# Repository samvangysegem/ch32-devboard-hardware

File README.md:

# CH32 Development Board

This repository contains hardware design files and documentation for a development board based on the CH32V30x series of microcontrollers. The board features USB-FS and UART communication interfaces, as well as input current monitoring. It is intended as a test and development platform for projects using the CH32V30x family.

Documentation is available in the [docs](./docs) folder, including:
- [Component datasheets and specifications](./docs/01_specs/)
- [Design calculations](./docs/02_calcs/)

For compatible firmware, see the related firmware repository
➡️ [ch32-devboard-firmware](https://github.com/samvangysegem/ch32-devboard-firmware)

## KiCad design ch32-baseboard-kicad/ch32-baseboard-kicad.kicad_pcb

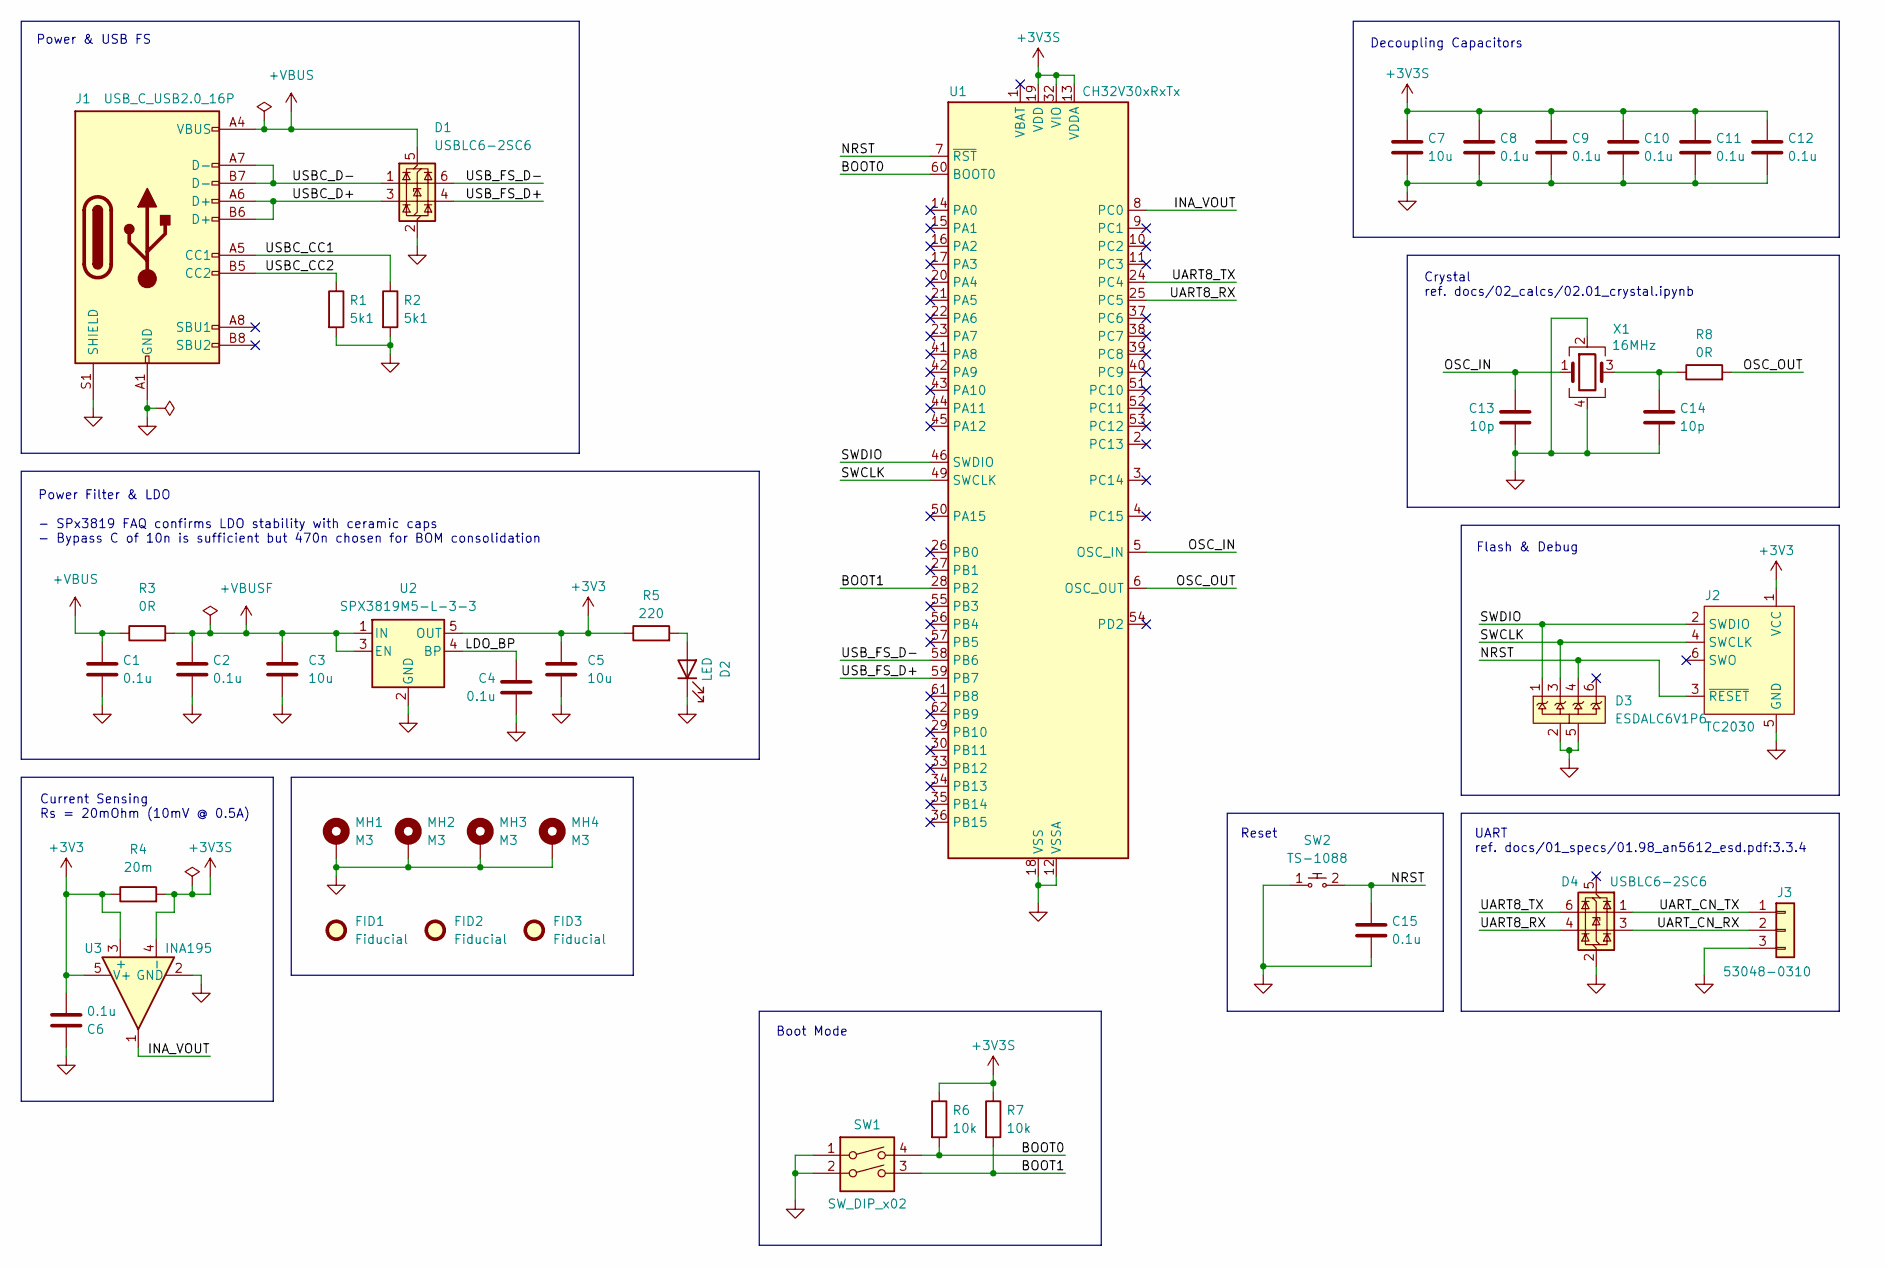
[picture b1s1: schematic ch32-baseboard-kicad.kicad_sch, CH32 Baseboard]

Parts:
C1, C2, C4, C6, C8, C9, C10, C11, C12, C15: 0.1u; C_0402_1005Metric; Manufacturer Part Number CL05B104KO5NNNC
C3, C5, C7: 10u; C_0805_2012Metric; Manufacturer Part Number CL21A106KAYNNNE
C13, C14: 10p; C_0402_1005Metric; Manufacturer Part Number CL05C100JB5NNNC
D1, D4: USBLC6-2SC6; SOT-23-6
D2: LED; LED_0603_1608Metric; Manufacturer Part Number KT-0603W
D3: ESDALC6V1P6; SOT-666IP-STM; Manufacturer Part Number ESDALC6V1P6
FID1, FID2, FID3: Fiducial; Fiducial_1mm_Mask2mm
J1: USB_C_USB2.0_16P; USB_C_Receptacle_GCT_USB4105-xx-A_16P_TopMnt_Horizontal; Manufacturer Part Number TYPE-C 16PIN 2MD(073); JLCPCB Part Number C2765186
J2: TC2030; Tag-Connect_TC2030-IDC-FP_2x03_P1.27mm_Vertical
J3: 53048-0310; Molex_PicoBlade_53048-0310_1x03_P1.25mm_Horizontal; Manufacturer Part Number 530480310
MH1, MH2, MH3, MH4: M3; MountingHole_3.2mm_M3_Pad_Via
R1, R2: 5k1; R_0402_1005Metric; Manufacturer Part Number 0402WGF5101TCE
R3: 0R; R_0805_2012Metric_Pad1.20x1.40mm_HandSolder; Manufacturer Part Number 0805W8F0000T5E
R4: 20m; R_1206_3216Metric; Manufacturer Part Number LR1206-21R020F4
R5: 220; R_0603_1608Metric; Manufacturer Part Number 0603WAF2200T5E
R6, R7: 10k; R_0603_1608Metric; Manufacturer Part Number 0603WAF1002T5E
R8: 0R; R_0402_1005Metric; Manufacturer Part Number 0402WGF0000TCE
SW1: SW_DIP_x02; SW_DIP_SPSTx02_Slide_6.7x6.64mm_W8.61mm_P2.54mm_LowProfile; Manufacturer Part Number SMXS-02K-TP
SW2: TS-1088; SW_SPST_TS-1088-xR020; Manufacturer Part Number TS-1088-AR02016
U1: CH32V30xRxTx; LQFP-64_10x10mm_P0.5mm; JLCPCB C2988083
U2: SPX3819M5-L-3-3; SOT-23-5; Manufacturer Part Number SPX3819M5-L-3-3/TR
U3: INA195; SOT-23-5
X1: 16MHz; Crystal_SMD_3225-4Pin_3.2x2.5mm; Manufacturer Part Number X322516MLB4SI

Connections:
+3V3: C5.1, C6.2, J2.1 (VCC), R4.1, R5.1, U2.5 (OUT), U3.3 (+), U3.5 (V+)
+3V3S: C7.1, C8.1, C9.1, C10.1, C11.1, C12.1, R4.2, R6.1, R7.1, U1.13 (VDDA), U1.19 (VDD), U1.32 (VIO), U1.48 (VDD), U1.64 (VIO), U3.4 (-)
+VBUS: C1.1, D1.5 (VBUS), J1.A4 (VBUS), J1.A9 (VBUS), J1.B4 (VBUS), J1.B9 (VBUS), R3.1
+VBUSF: C2.1, C3.1, R3.2, U2.1 (IN), U2.3 (EN)
/BOOT0: R6.2, SW1.4, U1.60 (BOOT0)
/BOOT1: R7.2, SW1.3, U1.28 (PB2)
/INA_VOUT: U1.8 (PC0), U3.1
/LDO_BP: C4.1, U2.4 (BP)
/NRST: C15.1, D3.4, J2.3 (~RESET), SW2.2, U1.7 (~RST)
/OSC_IN: C13.1, U1.5 (OSC_IN), X1.1
/OSC_OUT: R8.2, U1.6 (OSC_OUT)
/SWCLK: D3.3, J2.4 (SWCLK), U1.49 (SWCLK)
/SWDIO: D3.1, J2.2 (SWDIO), U1.46 (SWDIO)
/UART8_RX: D4.4 (I/O2), U1.25 (PC5)
/UART8_TX: D4.6 (I/O1), U1.24 (PC4)
/UART_CN_RX: D4.3 (I/O2), J3.2
/UART_CN_TX: D4.1 (I/O1), J3.1
/USBC_CC1: J1.A5 (CC1), R2.1
/USBC_CC2: J1.B5 (CC2), R1.1
/USBC_D+: D1.3 (I/O2), J1.A6 (D+), J1.B6 (D+)
/USBC_D-: D1.1 (I/O1), J1.A7 (D-), J1.B7 (D-)
/USB_FS_D+: D1.4 (I/O2), U1.59 (PB7)
/USB_FS_D-: D1.6 (I/O1), U1.58 (PB6)
GND: C1.2, C2.2, C3.2, C4.2, C5.2, C6.1, C7.2, C8.2, C9.2, C10.2, C11.2, C12.2, C13.2, C14.2, C15.2, D1.2 (GND), D2.1 (K), D3.2, D3.5, D4.2 (GND), J1.A1 (GND), J1.A12 (GND), J1.B1 (GND), J1.B12 (GND), J1.S1 (SHIELD), J2.5 (GND), J3.3, MH1.1, MH2.1, MH3.1, MH4.1, R1.2, R2.2, SW1.1, SW1.2, SW2.1, U1.12 (VSSA), U1.18 (VSS), U1.31 (VSS), U1.47 (VSS), U1.63 (VSS), U2.2 (GND), U3.2 (GND), X1.2, X1.4
unnamed: C14.1, R8.1, X1.3
unnamed: D2.2 (A), R5.2

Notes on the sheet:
UART ref. docs/01_specs/01.98_an5612_esd.pdf:3.3.4
Current Sensing Rs = 20mOhm (10mV @ 0.5A)
Reset
Crystal ref. docs/02_calcs/02.01_crystal.ipynb
Power & USB FS
Decoupling Capacitors
Boot Mode
Flash & Debug
Power Filter & LDO - SPx3819 FAQ confirms LDO stability with ceramic caps - Bypass C of 10n is sufficient but 470n chosen for BOM consolidation

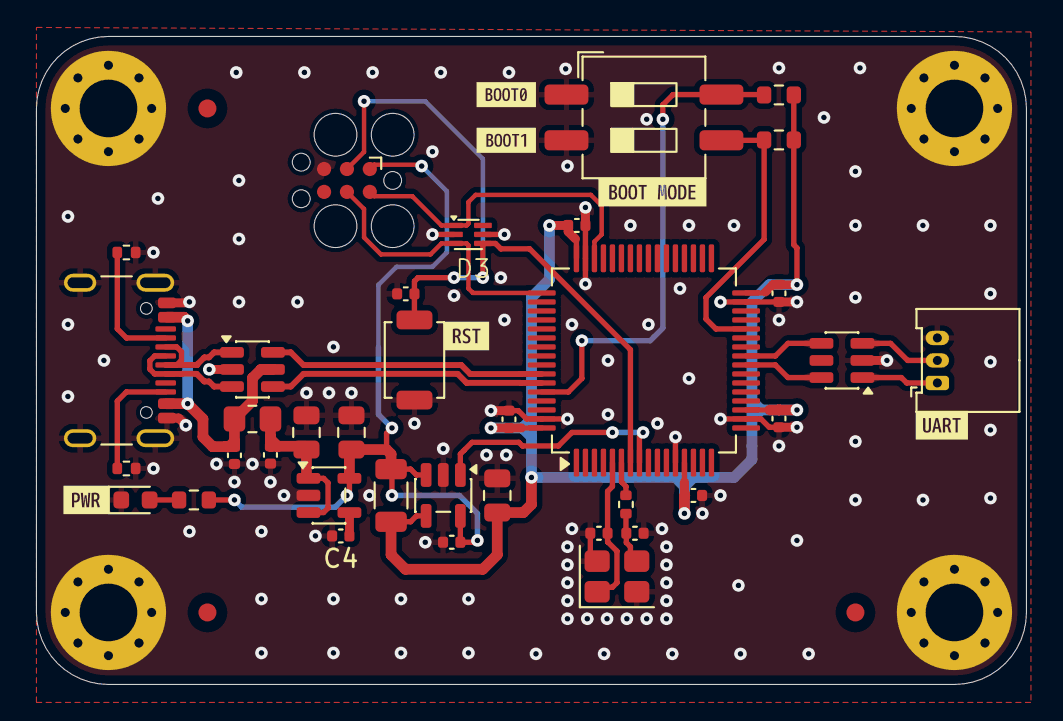
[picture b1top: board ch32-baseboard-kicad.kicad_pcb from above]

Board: 4 copper layers, 55.0 x 36.0 mm, 49 parts (0 on the bottom side), 26 nets.

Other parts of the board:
kibuzzard-692C82B7: G***; kibuzzard-692C82B7
kibuzzard-692C82FA: G***; kibuzzard-692C82FA
kibuzzard-692C811E: G***; kibuzzard-692C811E
kibuzzard-692C8041: G***; kibuzzard-692C8041
kibuzzard-6935C0F9: G***; kibuzzard-6935C0F9
kibuzzard-6935C105: G***; kibuzzard-6935C105

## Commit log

2025-12-10 feat: ch32 baseboard v1.1
2025-12-14 chore: cleanup
